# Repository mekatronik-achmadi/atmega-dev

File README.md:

# ATMega Development

This repository store some examples of ATMega development. Currently reworked

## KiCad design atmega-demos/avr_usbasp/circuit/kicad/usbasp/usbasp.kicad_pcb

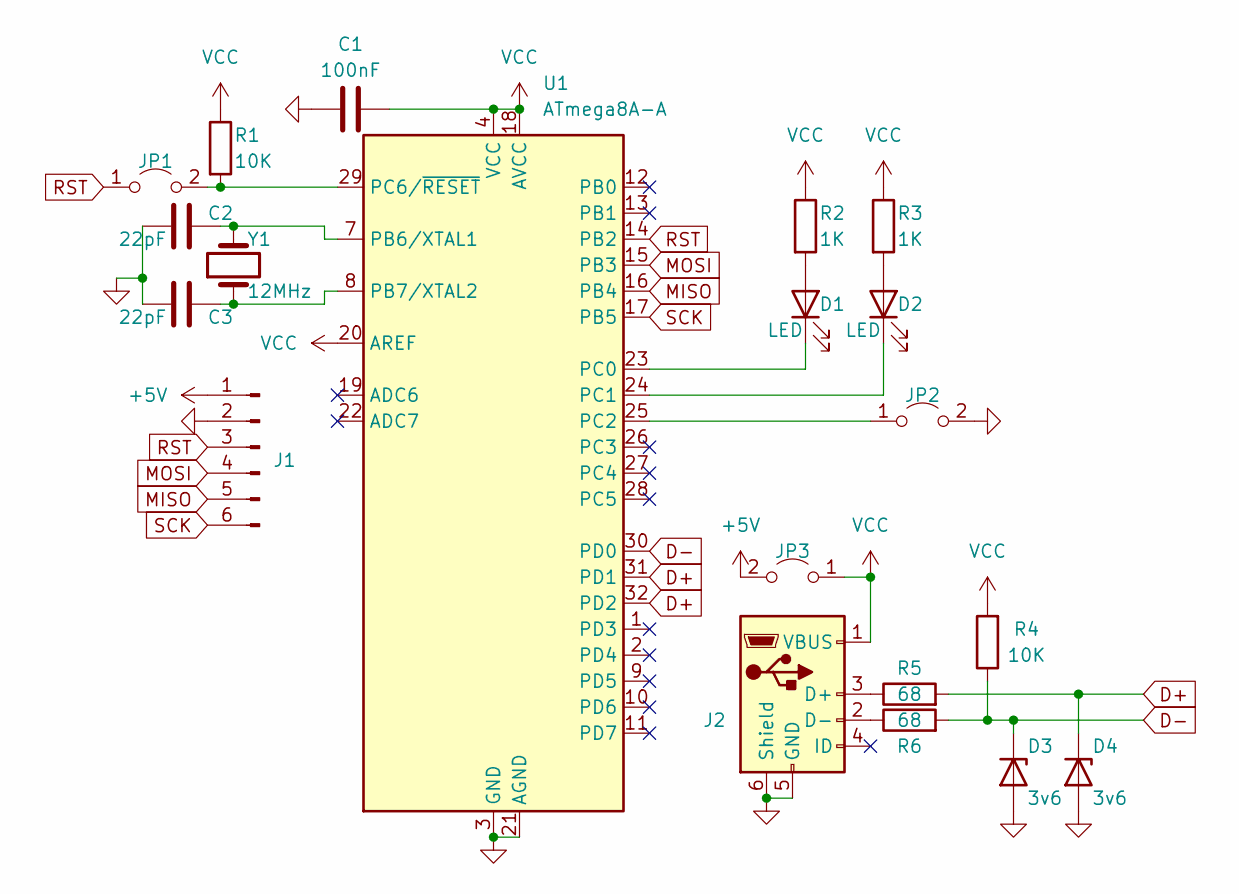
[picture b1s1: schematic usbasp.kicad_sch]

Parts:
C1: 100nF; C_0805_2012Metric_Pad1.18x1.45mm_HandSolder
C2, C3: 22pF; C_0805_2012Metric_Pad1.18x1.45mm_HandSolder
D1, D2: LED; LED_0805_2012Metric_Pad1.15x1.40mm_HandSolder
D3, D4: 3v6; D_SOD-323
J1: Conn_01x06_Pin; PinHeader_1x06_P2.00mm_Vertical
J2: USB_B_Mini; USB_Mini-B_Wuerth_65100516121_Horizontal
JP1, JP2, JP3: Jumper_2_Open; SolderJumper-2_P1.3mm_Open_RoundedPad1.0x1.5mm
R1, R4: 10K; R_0805_2012Metric_Pad1.20x1.40mm_HandSolder
R2, R3: 1K; R_0805_2012Metric_Pad1.20x1.40mm_HandSolder
R5, R6: 68; R_0805_2012Metric_Pad1.20x1.40mm_HandSolder
U1: ATmega8A-A; TQFP-32_7x7mm_P0.8mm
Y1: 12MHz; Crystal_SMD_HC49-SD

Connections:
+5V: J1.1, JP3.2 (B)
D+: D4.1 (K), R5.2, U1.31 (PD1), U1.32 (PD2)
D-: D3.1 (K), R4.1, R6.2, U1.30 (PD0)
GND: C1.1, C2.1, C3.1, D3.2 (A), D4.2 (A), J1.2, J2.5 (GND), J2.6 (Shield), JP2.2 (B), U1.3 (GND), U1.5 (GND), U1.21 (AGND)
MISO: J1.5, U1.16 (PB4)
MOSI: J1.4, U1.15 (PB3)
unnamed: D1.2 (A), R2.2
unnamed: D1.1 (K), U1.23 (PC0)
unnamed: D2.2 (A), R3.2
unnamed: D2.1 (K), U1.24 (PC1)
unnamed: J2.3 (D+), R5.1
unnamed: J2.2 (D-), R6.1
unnamed: JP1.2 (B), R1.2, U1.29 (PC6/~RESET)
unnamed: JP2.1 (A), U1.25 (PC2)
unnamed: C2.2, U1.7 (PB6/XTAL1), Y1.2
unnamed: C3.2, U1.8 (PB7/XTAL2), Y1.1
RST: J1.3, JP1.1 (A), U1.14 (PB2)
SCK: J1.6, U1.17 (PB5)
VCC: C1.2, J2.1 (VBUS), JP3.1 (A), R1.1, R2.1, R3.1, R4.2, U1.4 (VCC), U1.6 (VCC), U1.18 (AVCC), U1.20 (AREF)

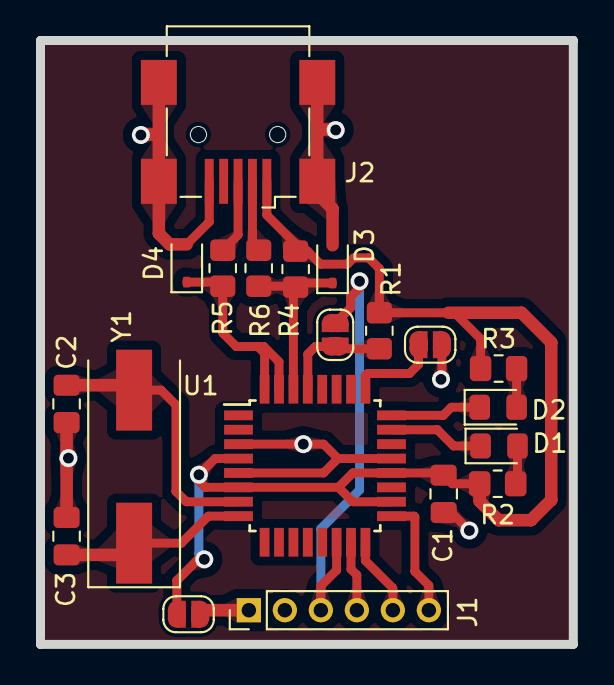
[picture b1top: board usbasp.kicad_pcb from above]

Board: 2 copper layers, 29.6 x 33.6 mm, 20 parts (0 on the bottom side), 19 nets.

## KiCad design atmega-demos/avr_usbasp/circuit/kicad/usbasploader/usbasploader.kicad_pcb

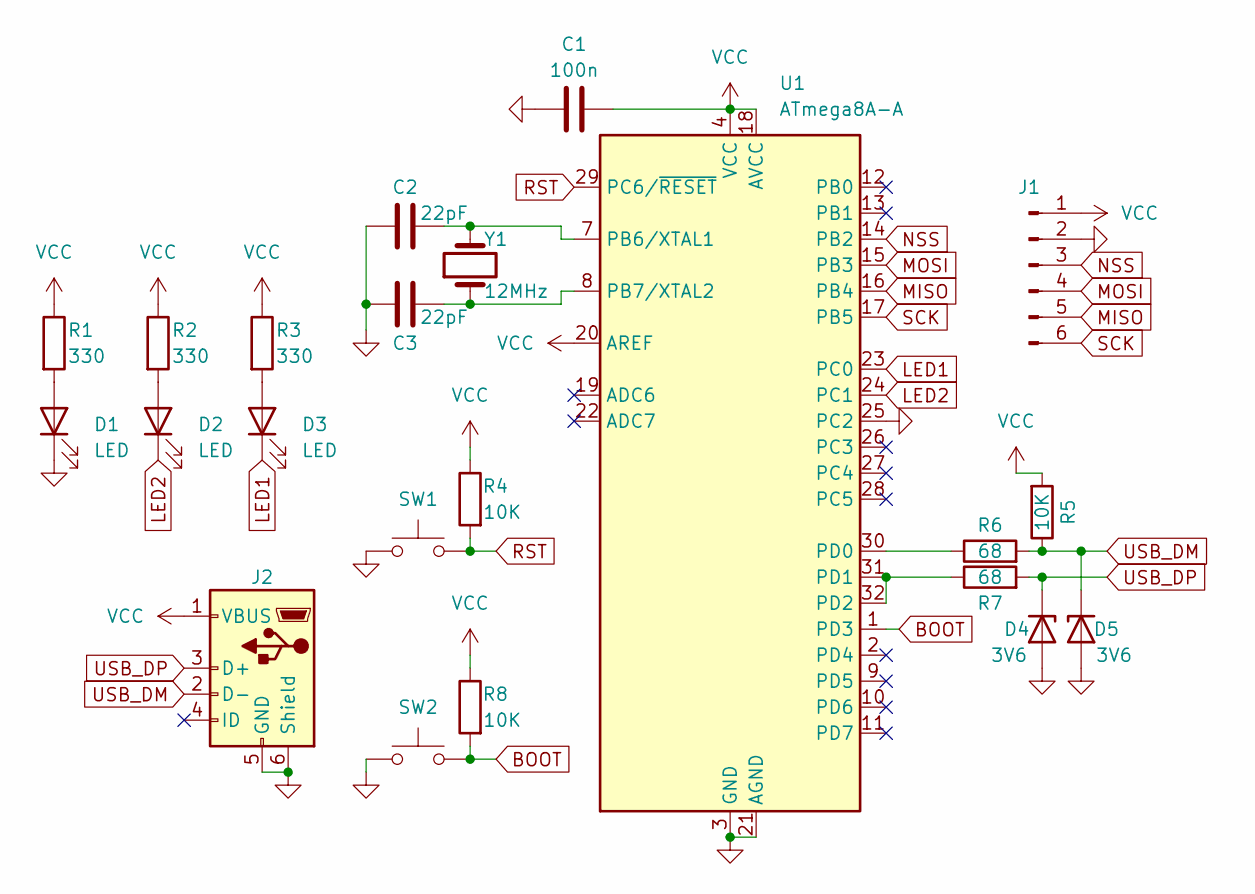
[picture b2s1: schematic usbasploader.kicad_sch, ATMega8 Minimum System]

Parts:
C1: 100n; C_0805_2012Metric_Pad1.18x1.45mm_HandSolder
C2, C3: 22pF; C_0805_2012Metric_Pad1.18x1.45mm_HandSolder
D1, D2, D3: LED; LED_0805_2012Metric_Pad1.15x1.40mm_HandSolder
D4, D5: 3V6; D_SOD-323
J1: Conn_01x06_Pin; PinHeader_1x06_P2.54mm_Vertical
J2: USB_B_Mini; USB_Mini-B_Wuerth_65100516121_Horizontal
R1, R2, R3: 330; R_0805_2012Metric_Pad1.20x1.40mm_HandSolder
R4, R5, R8: 10K; R_0805_2012Metric_Pad1.20x1.40mm_HandSolder
R6, R7: 68; R_0805_2012Metric_Pad1.20x1.40mm_HandSolder
SW1, SW2: SW_Push; SW_Tactile_SPST_NO_Straight_CK_PTS636Sx25SMTRLFS
U1: ATmega8A-A; TQFP-32_7x7mm_P0.8mm
Y1: 12MHz; Crystal_SMD_HC49-SD

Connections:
BOOT: R8.2, SW2.2, U1.1 (PD3)
GND: C1.1, C2.1, C3.1, D1.1 (K), D4.2 (A), D5.2 (A), J1.2, J2.5 (GND), J2.6 (Shield), SW1.1, SW2.1, U1.3 (GND), U1.5 (GND), U1.21 (AGND), U1.25 (PC2)
LED1: D3.1 (K), U1.23 (PC0)
LED2: D2.1 (K), U1.24 (PC1)
MISO: J1.5, U1.16 (PB4)
MOSI: J1.4, U1.15 (PB3)
NSS: J1.3, U1.14 (PB2)
unnamed: D1.2 (A), R1.2
unnamed: D2.2 (A), R2.2
unnamed: D3.2 (A), R3.2
unnamed: C2.2, U1.7 (PB6/XTAL1), Y1.2
unnamed: C3.2, U1.8 (PB7/XTAL2), Y1.1
unnamed: R6.1, U1.30 (PD0)
unnamed: R7.1, U1.31 (PD1), U1.32 (PD2)
RST: R4.2, SW1.2, U1.29 (PC6/~RESET)
SCK: J1.6, U1.17 (PB5)
USB_DM: D5.1 (K), J2.2 (D-), R5.1, R6.2
USB_DP: D4.1 (K), J2.3 (D+), R7.2
VCC: C1.2, J1.1, J2.1 (VBUS), R1.1, R2.1, R3.1, R4.1, R5.2, R8.1, U1.4 (VCC), U1.6 (VCC), U1.18 (AVCC), U1.20 (AREF)

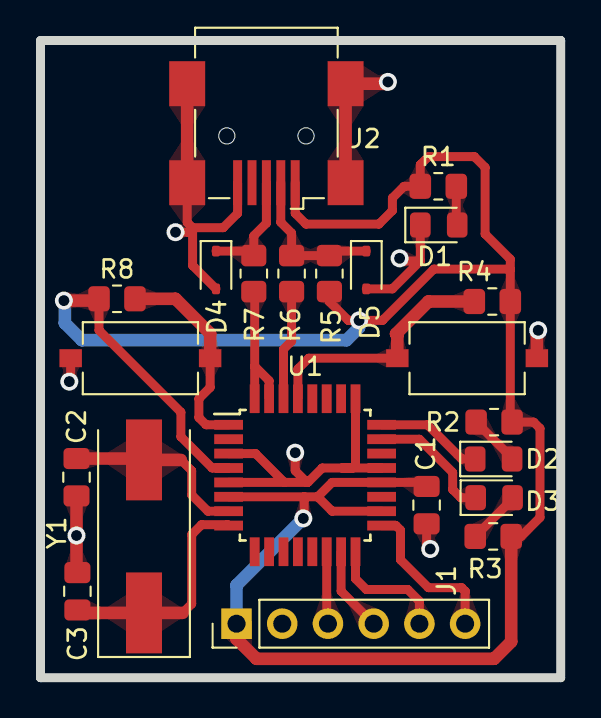
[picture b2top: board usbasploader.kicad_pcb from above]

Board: 2 copper layers, 28.9 x 35.4 mm, 22 parts (0 on the bottom side), 19 nets.

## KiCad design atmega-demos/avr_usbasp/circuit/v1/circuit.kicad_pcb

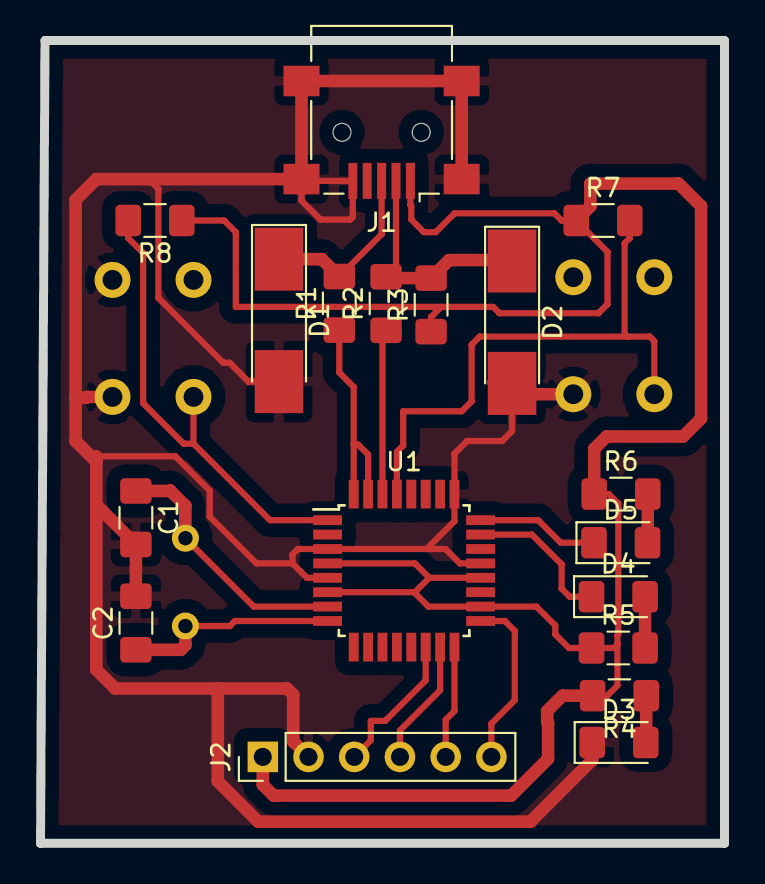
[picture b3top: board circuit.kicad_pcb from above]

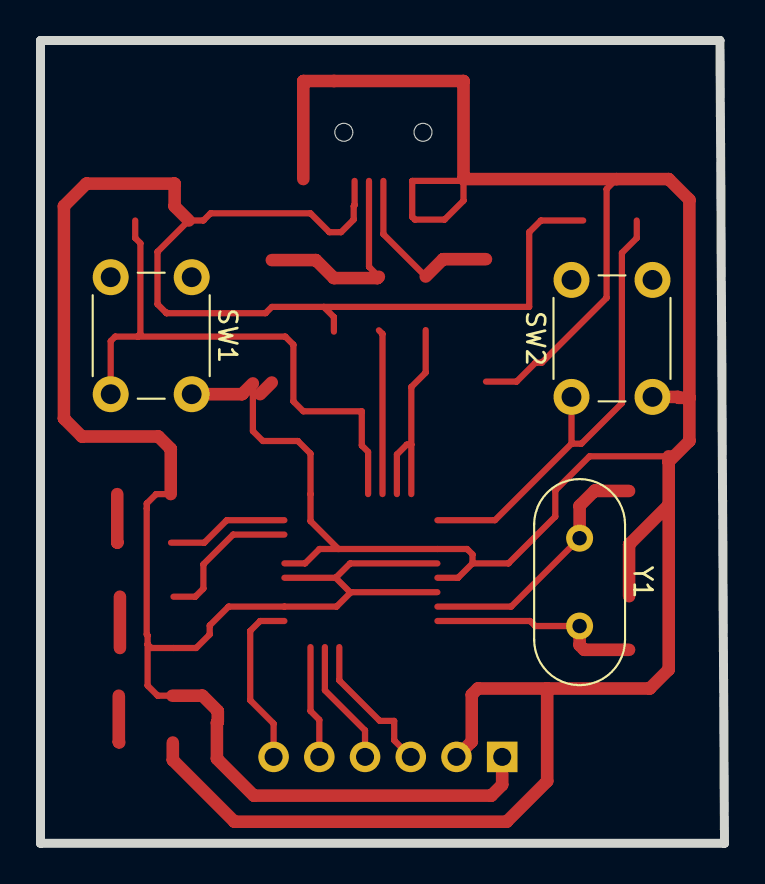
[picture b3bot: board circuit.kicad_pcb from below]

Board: 2 copper layers, 38.0 x 44.6 mm, 21 parts (3 on the bottom side), 19 nets.

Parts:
C1, C2: 22p; C_1206_3216Metric_Pad1.42x1.75mm_HandSolder
D1, D2: D_Zener; D_MELF_Handsoldering
D3, D4, D5: LED; LED_1206_3216Metric_Pad1.42x1.75mm_HandSolder
J1: USB_B_Mini; USB_Mini-B_Lumberg_2486_01_Horizontal
J2: ISP; PinHeader_1x06_P2.54mm_Vertical
R1, R2: 68; R_1206_3216Metric_Pad1.42x1.75mm_HandSolder
R3, R7, R8: 2k2; R_1206_3216Metric_Pad1.42x1.75mm_HandSolder
R4, R5, R6: 1k; R_1206_3216Metric_Pad1.42x1.75mm_HandSolder
SW1: RST; SW_PUSH_6mm
SW2: USER; SW_PUSH_6mm
U1: ATmega8A-AU; TQFP-32_7x7mm_P0.8mm
Y1: 12MHz; Crystal_HC49-4H_Vertical

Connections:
+5V: J1.1, J2.1, R3.1, R4.2, R5.1, R6.1, R7.1, R8.1, U1.4, U1.6, U1.18, U1.20
/D+: R1.1, U1.31, U1.32
/D-: R2.1, U1.30
/USER: R8.2, SW2.1, U1.1
GND: C1.2, C2.2, D1.2, D2.2, D3.1, J1.5, J1.6, J2.2, SW1.1, SW2.2, U1.3, U1.5, U1.21, U1.25
unnamed: C1.1, U1.7, Y1.1
unnamed: C2.1, U1.8, Y1.2
unnamed: D1.1, J1.3, R1.2
unnamed: D2.1, J1.2, R2.2, R3.2
unnamed: D3.2, R4.1
unnamed: D4.1, U1.23
unnamed: D4.2, R5.2
unnamed: D5.1, U1.24
unnamed: D5.2, R6.2
unnamed: J2.3, U1.14
unnamed: J2.4, U1.15
unnamed: J2.5, U1.16
unnamed: J2.6, U1.17
unnamed: R7.2, SW1.2, U1.29

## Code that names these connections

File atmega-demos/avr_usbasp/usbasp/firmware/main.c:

/*
 * USBasp - USB in-circuit programmer for Atmel AVR controllers
 *
 * Thomas Fischl <tfischl@gmx.de>
 *
 * License........: GNU GPL v2 (see Readme.txt)
 * Target.........: ATMega8 at 12 MHz
 * Creation Date..: 2005-02-20
 * Last change....: 2009-02-28
 *
 * PC2 SCK speed option.
 * GND  -> slow (8khz SCK),
 * open -> software set speed (default is 375kHz SCK)
 */

#include <avr/io.h>
#include <avr/interrupt.h>
#include <avr/pgmspace.h>
#include <avr/wdt.h>

#include "usbasp.h"
#include "usbdrv.h"
#include "isp.h"
#include "clock.h"
#include "tpi.h"
#include "tpi_defs.h"

static uchar replyBuffer[8];

static uchar prog_state = PROG_STATE_IDLE;
static uchar prog_sck = USBASP_ISP_SCK_AUTO;

static uchar prog_address_newmode = 0;
static unsigned long prog_address;
static unsigned int prog_nbytes = 0;
static unsigned int prog_pagesize;
static uchar prog_blockflags;
static uchar prog_pagecounter;

uchar usbFunctionSetup(uchar data[8]) {

	uchar len = 0;

	if (data[1] == USBASP_FUNC_CONNECT) {

		/* set SCK speed */
		if ((PINC & (1 << PC2)) == 0) {
			ispSetSCKOption(USBASP_ISP_SCK_8);
		} else {
			ispSetSCKOption(prog_sck);
		}

		/* set compatibility mode of address delivering */
		prog_address_newmode = 0;

		ledRedOn();
		ispConnect();

	} else if (data[1] == USBASP_FUNC_DISCONNECT) {
		ispDisconnect();
		ledRedOff();

	} else if (data[1] == USBASP_FUNC_TRANSMIT) {
		replyBuffer[0] = ispTransmit(data[2]);
		replyBuffer[1] = ispTransmit(data[3]);
		replyBuffer[2] = ispTransmit(data[4]);
		replyBuffer[3] = ispTransmit(data[5]);
		len = 4;

	} else if (data[1] == USBASP_FUNC_READFLASH) {

		if (!prog_address_newmode)
			prog_address = (data[3] << 8) | data[2];

		prog_nbytes = (data[7] << 8) | data[6];
		prog_state = PROG_STATE_READFLASH;
		len = 0xff; /* multiple in */

	} else if (data[1] == USBASP_FUNC_READEEPROM) {

		if (!prog_address_newmode)
			prog_address = (data[3] << 8) | data[2];

		prog_nbytes = (data[7] << 8) | data[6];
		prog_state = PROG_STATE_READEEPROM;
		len = 0xff; /* multiple in */

	} else if (data[1] == USBASP_FUNC_ENABLEPROG) {
		replyBuffer[0] = ispEnterProgrammingMode();
		len = 1;

	} else if (data[1] == USBASP_FUNC_WRITEFLASH) {

		if (!prog_address_newmode)
			prog_address = (data[3] << 8) | data[2];

		prog_pagesize = data[4];
		prog_blockflags = data[5] & 0x0F;
		prog_pagesize += (((unsigned int) data[5] & 0xF0) << 4);
		if (prog_blockflags & PROG_BLOCKFLAG_FIRST) {
			prog_pagecounter = prog_pagesize;
		}
		prog_nbytes = (data[7] << 8) | data[6];
		prog_state = PROG_STATE_WRITEFLASH;
		len = 0xff; /* multiple out */

	} else if (data[1] == USBASP_FUNC_WRITEEEPROM) {

		if (!prog_address_newmode)
			prog_address = (data[3] << 8) | data[2];

		prog_pagesize = 0;
		prog_blockflags = 0;
		prog_nbytes = (data[7] << 8) | data[6];
		prog_state = PROG_STATE_WRITEEEPROM;
		len = 0xff; /* multiple out */

	} else if (data[1] == USBASP_FUNC_SETLONGADDRESS) {

		/* set new mode of address delivering (ignore address delivered in commands) */
		prog_address_newmode = 1;
		/* set new address */
		prog_address = *((unsigned long*) &data[2]);

	} else if (data[1] == USBASP_FUNC_SETISPSCK) {

		/* set sck option */
		prog_sck = data[2];
		replyBuffer[0] = 0;
		len = 1;

	} else if (data[1] == USBASP_FUNC_TPI_CONNECT) {
		tpi_dly_cnt = data[2] | (data[3] << 8);

		/* RST high */
		ISP_OUT |= (1 << ISP_RST);
		ISP_DDR |= (1 << ISP_RST);

		clockWait(3);

		/* RST low */
		ISP_OUT &= ~(1 << ISP_RST);
		ledRedOn();

		clockWait(16);
		tpi_init();
	
	} else if (data[1] == USBASP_FUNC_TPI_DISCONNECT) {

		tpi_send_byte(TPI_OP_SSTCS(TPISR));
		tpi_send_byte(0);

		clockWait(10);

		/* pulse RST */
		ISP_OUT |= (1 << ISP_RST);
		clockWait(5);
		ISP_OUT &= ~(1 << ISP_RST);
		clockWait(5);

		/* set all ISP pins inputs */
		ISP_DDR &= ~((1 << ISP_RST) | (1 << ISP_SCK) | (1 << ISP_MOSI));
		/* switch pullups off */
		ISP_OUT &= ~((1 << ISP_RST) | (1 << ISP_SCK) | (1 << ISP_MOSI));

		ledRedOff();
	
	} else if (data[1] == USBASP_FUNC_TPI_RAWREAD) {
		replyBuffer[0] = tpi_recv_byte();
		len = 1;
	
	} else if (data[1] == USBASP_FUNC_TPI_RAWWRITE) {
		tpi_send_byte(data[2]);
	
	} else if (data[1] == USBASP_FUNC_TPI_READBLOCK) {
		prog_address = (data[3] << 8) | data[2];
		prog_nbytes = (data[7] << 8) | data[6];
		prog_state = PROG_STATE_TPI_READ;
		len = 0xff; /* multiple in */
	
	} else if (data[1] == USBASP_FUNC_TPI_WRITEBLOCK) {
		prog_address = (data[3] << 8) | data[2];
		prog_nbytes = (data[7] << 8) | data[6];
		prog_state = PROG_STATE_TPI_WRITE;
		len = 0xff; /* multiple out */
	
	} else if (data[1] == USBASP_FUNC_GETCAPABILITIES) {
		replyBuffer[0] = USBASP_CAP_0_TPI;
		replyBuffer[1] = 0;
		replyBuffer[2] = 0;
		replyBuffer[3] = 0;
		len = 4;
	}

	usbMsgPtr = replyBuffer;

	return len;
}

uchar usbFunctionRead(uchar *data, uchar len) {

	uchar i;

	/* check if programmer is in correct read state */
	if ((prog_state != PROG_STATE_READFLASH) && (prog_state
			!= PROG_STATE_READEEPROM) && (prog_state != PROG_STATE_TPI_READ)) {
		return 0xff;
	}

	/* fill packet TPI mode */
	if(prog_state == PROG_STATE_TPI_READ)
	{
		tpi_read_block(prog_address, data, len);
		prog_address += len;
		return len;
	}

	/* fill packet ISP mode */
	for (i = 0; i < len; i++) {
		if (prog_state == PROG_STATE_READFLASH) {
			data[i] = ispReadFlash(prog_address);
		} else {
			data[i] = ispReadEEPROM(prog_address);
		}
		prog_address++;
	}

	/* last packet? */
	if (len < 8) {
		prog_state = PROG_STATE_IDLE;
	}

	return len;
}

uchar usbFunctionWrite(uchar *data, uchar len) {

	uchar retVal = 0;
	uchar i;

	/* check if programmer is in correct write state */
	if ((prog_state != PROG_STATE_WRITEFLASH) && (prog_state
			!= PROG_STATE_WRITEEEPROM) && (prog_state != PROG_STATE_TPI_WRITE)) {
		return 0xff;
	}

	if (prog_state == PROG_STATE_TPI_WRITE)
	{
		tpi_write_block(prog_address, data, len);
		prog_address += len;
		prog_nbytes -= len;
		if(prog_nbytes <= 0)
		{
			prog_state = PROG_STATE_IDLE;
			return 1;
		}
		return 0;
	}

	for (i = 0; i < len; i++) {

		if (prog_state == PROG_STATE_WRITEFLASH) {
			/* Flash */

			if (prog_pagesize == 0) {
				/* not paged */
				ispWriteFlash(prog_address, data[i], 1);
			} else {
				/* paged */
				ispWriteFlash(prog_address, data[i], 0);
				prog_pagecounter--;
				if (prog_pagecounter == 0) {
					ispFlushPage(prog_address, data[i]);
					prog_pagecounter = prog_pagesize;
				}
			}

		} else {
			/* EEPROM */
			ispWriteEEPROM(prog_address, data[i]);
		}

		prog_nbytes--;

		if (prog_nbytes == 0) {
			prog_state = PROG_STATE_IDLE;
			if ((prog_blockflags & PROG_BLOCKFLAG_LAST) && (prog_pagecounter
					!= prog_pagesize)) {

				/* last block and page flush pending, so flush it now */
				ispFlushPage(prog_address, data[i]);
			}

			retVal = 1; // Need to return 1 when no more data is to be received
		}

		prog_address++;
	}

	return retVal;
}

int main(void) {
	uchar i, j;

	/* no pullups on USB and ISP pins */
	PORTD = 0;
	PORTB = 0;
	/* all outputs except PD2 = INT0 */
	//DDRD = ~(1 << 2);

	/* output SE0 for USB reset */
	DDRB = ~0;
	DDRD = ~0;
	
	j = 0;
	/* USB Reset by device only required on Watchdog Reset */
	while (--j) {
		i = 0;
		/* delay >10ms for USB reset */
		while (--i)
			;
	}
	/* all USB and ISP pins inputs */
	DDRB = 0;
	DDRD = 0;

	/* all inputs except PC0, PC1 */
	DDRC = 0x03;
	PORTC = 0xfe;

	/* init timer */
	clockInit();

	/* main event loop */
	usbInit();
	sei();
	for (;;) {
		usbPoll();
	}
	return 0;
}

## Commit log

2020-11-13 update terminal
2020-11-13 serial terminal
2020-11-13 optdepend serial terminal
2023-10-10 Desktop Menu
2023-10-19 Add Readme
2023-10-19 KiCAD Rework M8 Board
2023-10-19 KiCAD Rework MinSys
2023-10-19 KiCad Rework
2023-10-19 USBAsp KiCAD
2023-10-19 USBASP Loader PCB
2023-10-19 USBAsp PCB
2023-10-19 Reworked
2023-10-19 restructure untested sources
2023-10-19 ATMega Demos checking
2023-10-20 Simulation based on SimAVR
2023-10-20 SimAVR
2023-12-19 New Qt Serial Terminal
2023-12-19 Qt Serial Terminal
2023-12-19 Try to package on Arch
2023-12-19 Packaging on Arch
2024-03-18 wxSerial
2024-03-18 Use Newest Qt Serial Terminal
2024-03-18 FLTK Serial Terminal
2024-03-18 FLTK Serial
2024-03-18 FLTK Serial Gui
2024-03-19 FLTK Serial still failed
2024-03-19 Drop Failed Serial FLTK
2024-03-20 wxWidget Serial
